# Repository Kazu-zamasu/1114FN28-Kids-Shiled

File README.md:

1114FN28-Kids-Shiled
==================================
超簡単な概要
#趣旨
mbedなりArduinoなりでArduino Pin Cnvertible の場合に高級なシールドだけじゃなく子供でも遊べる簡単なシールドを作る。  
Lチカでもモーターでも遊べるように。また、コードから制御するのではなく、視覚的、感覚的に分かりやすいVolや照度や温度などで遊べる基本的な制御を学べるボードにする。  
できれば、販売価格は小学校高学年とかその年齢層でもお年玉とか、日頃のプレゼントで買って貰えそうな値段に抑えたい。  
尚、本プロジェクトは完全ボランティアなので必要な経費をそのまま売価にします。よって、設計費用等の人件費はいっさい含みません。実際にお金を支払うもの以外は完全手弁当プロジェクトです。（とりあえず）

//ピン仕様:Arduinoピン配列に準拠  
ピン仕様はスイッチサイエンス　mbed 1114FN28  
mbed LPC1114FN28  に対応としました。
http://www.switch-science.com/catalog/1714/  

##最終仕様：Rev0
mbed 1114FN28 に対応するのでプロジェクト名自体を変更
###ハード仕様
１）ボリュームによるアナログ入力  
２）LED２個（5v抵抗あり）緑・赤  
３）最大９A　MOS-FET(モータドライバ兼用） 
４）フォトICによる照度のアナログ入力  
５）サーミスタによる温度のアナログ入力  
６）タクトスイッチ２個によるデジタル入力  
７）トグルスイッチによるデジタル入力  

##改訂前  
####ハード仕様（must)  
1)可変抵抗２つ（ノブ付）  
2)フォトトランジスタ１つ  
3)LED4つ  赤・青・緑・黄
4)最大3V、2Aのモータドライバ出力2つ（FA130、3VStall電流値より）  
5)サーミスター２つ  
6)単３電池ボックス  
7)3Pスイッチ1つ、2Pスイッチ1つ  

####ハード仕様(Addtional)  
1)電圧入力を入れる場合は逆接保護回路  
2)全てリード部品にて接続。なるべく表面実装を避ける  
3)可能なら7セグ  
4)
な感じ。適時アプデします。 
上記のAuduinoシールドはこれをクローズしたら考えます。

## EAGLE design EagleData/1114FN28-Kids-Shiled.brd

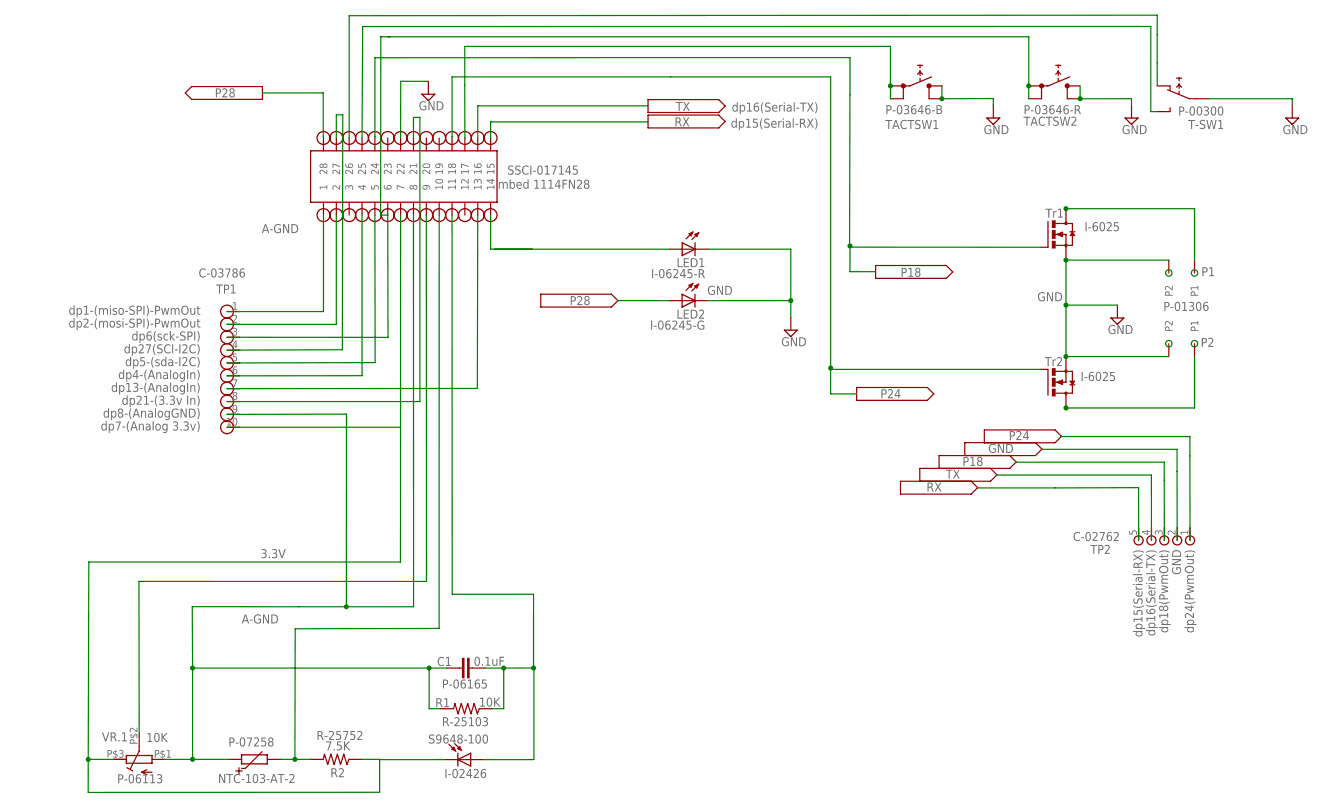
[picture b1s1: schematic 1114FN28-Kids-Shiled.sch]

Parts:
0-50C: NTC-103-AT-2; NTC
C1: 0.1uF; C
LED1: I-06245-R; LED5MM
LED2: I-06245-G; LED5MM
R1: 10K; R12MM
R2: 7.5K; R12MM
T-SW1: P-00300; TOGLE-SW
TACTSW1: P-03646-B; TACT-SW
TACTSW2: P-03646-R; TACT-SW
TB1, TB2: P-01306; TB
U$1: FH-1X14; DIP28-SOCKET
U$2: S9648-100; PHOTO-IC
U$3: SIPS-5
U$4, U$5: I-6025; TO251AA
U$8: SIPS-10
VR.1: 10K; VOL-TRIM

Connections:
3.3V: R2.1, U$1.P$7 (7), U$2.P$2 (C), U$8.10, VR.1.P$3 (E)
A-GND: 0-50C.1, C1.1, R1.2, U$1.P$8 (8), U$8.9, VR.1.P$1 (A)
GND: LED1.K (C), LED2.K (C), T-SW1.P$2 (2COM), TACTSW1.1 (4), TACTSW1.2, TACTSW2.1 (4), TACTSW2.2, TB1.P$2 (P2), TB2.P$2 (P2), U$1.P$22 (22), U$3.2, U$4.3 (S), U$5.3 (S)
unnamed: C1.2, R1.1, U$1.P$11 (11), U$2.P$1 (A)
unnamed: U$1.P$9 (9), VR.1.P$2 (S)
unnamed: TACTSW1.3, TACTSW1.4 (1), U$1.P$17 (17)
unnamed: U$1.P$1 (1), U$8.1
unnamed: U$1.P$5 (5), U$8.5
unnamed: U$1.P$27 (27), U$8.4
unnamed: T-SW1.P$3 (3), U$1.P$25 (25)
unnamed: U$1.P$2 (2), U$8.2
unnamed: TACTSW2.3, TACTSW2.4 (1), U$1.P$6 (6), U$8.3
unnamed: U$1.P$4 (4), U$8.6
unnamed: T-SW1.P$1 (1), U$1.P$26 (26)
unnamed: TB2.P$1 (P1), U$5.2 (D), U$5.4 (D)
unnamed: TB1.P$1 (P1), U$4.2 (D), U$4.4 (D)
unnamed: U$1.P$13 (13), U$8.7
unnamed: 0-50C.2, R2.2, U$1.P$10 (10)
unnamed: U$1.P$21 (21), U$8.8
P14: LED1.A, U$1.P$14 (14)
P18: U$1.P$18 (18), U$3.3, U$4.1 (G)
P24: U$1.P$24 (24), U$3.1, U$5.1 (G)
P28: LED2.A, U$1.P$28 (28)
RX: U$1.P$15 (15), U$3.5
TX: U$1.P$16 (16), U$3.4

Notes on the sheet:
dp13-(AnalogIn)
dp1-(miso-SPI)-PwmOut
dp2-(mosi-SPI)-PwmOut
dp6(sck-SPI)
dp27(SCl-I2C)
dp5-(sda-I2C)
dp4-(AnalogIn)
dp15(Serial-RX)
dp16(Serial-TX)
dp8-(AnalogGND)
TP1
Tr1
Tr2
mbed 1114FN28
P-01306
P-07258
P-06113
R-25103
P-06165
R-25752
I-02426
C-03786
SSCI-017145
dp21-(3.3v In)
TP2
C-02762
dp7-(Analog 3.3v)
dp24(PwmOut)
GND
dp18(PwmOut)

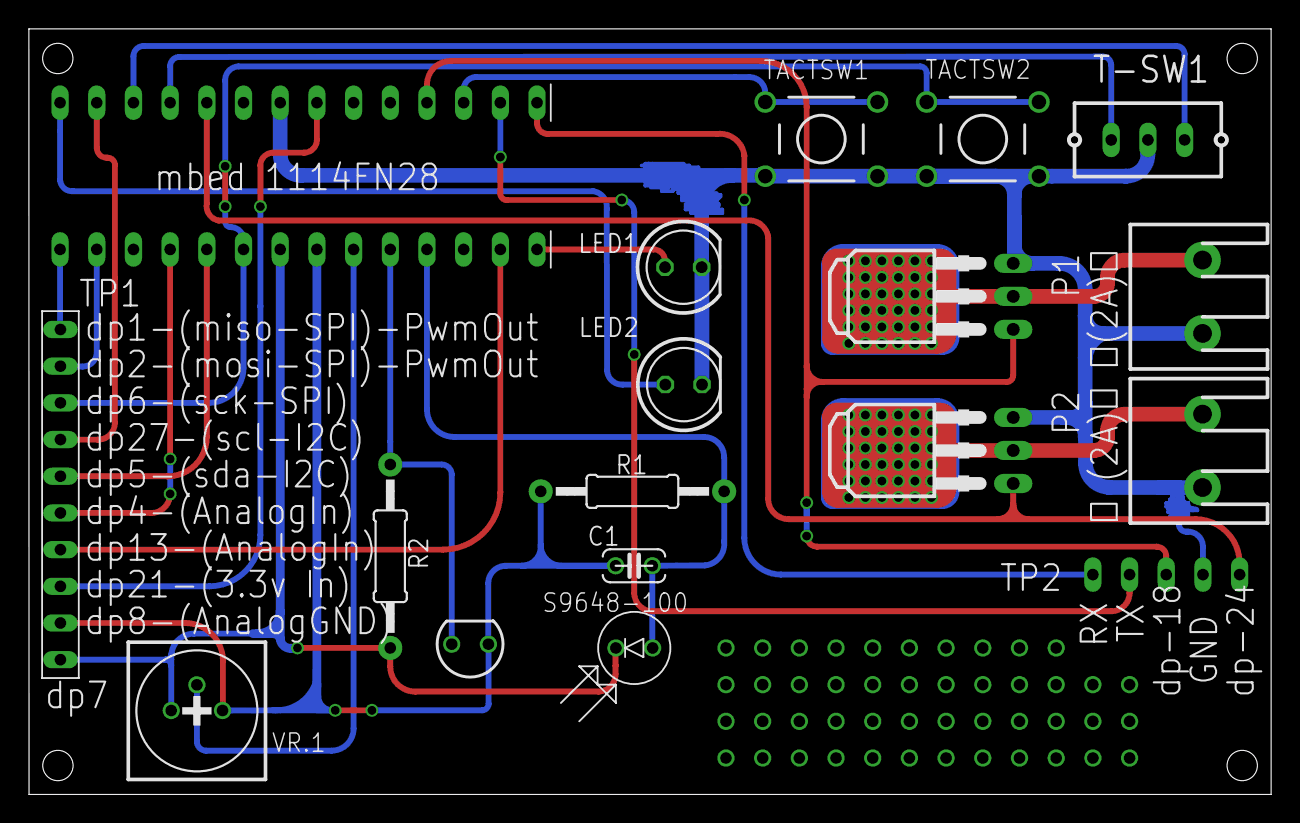
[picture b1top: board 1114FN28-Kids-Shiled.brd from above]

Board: 2 copper layers, 86.0 x 53.0 mm, 19 parts (1 on the bottom side), 25 nets.

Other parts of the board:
U$7: A4L-LOC

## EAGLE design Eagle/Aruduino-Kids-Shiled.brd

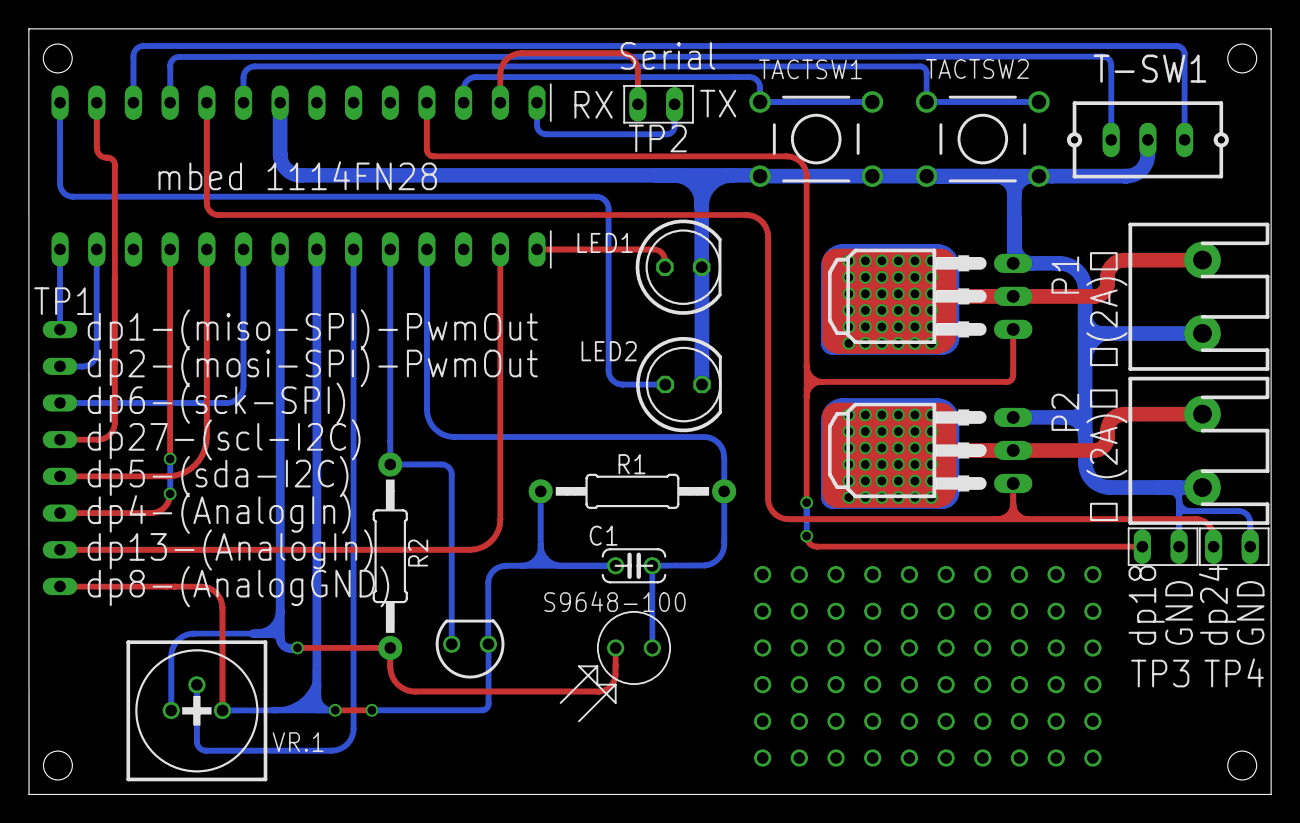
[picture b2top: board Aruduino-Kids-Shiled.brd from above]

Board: 2 copper layers, 86.0 x 53.0 mm, 21 parts (0 on the bottom side), 25 nets.

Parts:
0-50C: NTC-103-AT-2; NTC
C1: 0.1uF; C
LED1: I-06245-R; LED5MM
LED2: I-06245-G; LED5MM
R1: 10K; R12MM
R2: 7.5K; R12MM
T-SW1: P-00300; TOGLE-SW
TACTSW1: P-03646-B; TACT-SW
TACTSW2: P-03646-R; TACT-SW
TB1, TB2: P-01306; TB
U$1: FH-1X14; DIP28-SOCKET
U$2: S9648-100; PHOTO-IC
U$3: SIPS-7; SIPC-7
U$4: IR-6050; TO251AA
U$5: IR6050; TO251AA
U$6, U$9, U$10: SIPS-2; SIPC-2
U$7: A4L-LOC
VR.1: 10K; VOL-TRIM

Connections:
3.3V: R2.1, U$1.P$7, U$2.P$2, VR.1.P$3
A-GND: 0-50C.1, C1.1, R1.2, U$1.P$8, U$3.P$8, VR.1.P$1
GND: LED1.K, LED2.K, T-SW1.P$2, TACTSW1.1, TACTSW1.2, TACTSW2.1, TACTSW2.2, TB1.P$2, TB2.P$2, U$1.P$22, U$4.3, U$5.3, U$9.P$2, U$10.P$2
unnamed: C1.2, R1.1, U$1.P$11, U$2.P$1
unnamed: U$1.P$9, VR.1.P$2
unnamed: TACTSW1.3, TACTSW1.4, U$1.P$17
unnamed: U$1.P$1, U$3.P$1
unnamed: TACTSW2.3, TACTSW2.4, U$1.P$23
unnamed: U$1.P$27, U$3.P$4
unnamed: T-SW1.P$3, U$1.P$25
unnamed: U$1.P$2, U$3.P$2
unnamed: U$1.P$6, U$3.P$3
unnamed: U$1.P$5, U$3.P$5
unnamed: U$1.P$4, U$3.P$6
unnamed: T-SW1.P$1, U$1.P$26
unnamed: TB2.P$1, U$5.2, U$5.4
unnamed: TB1.P$1, U$4.2, U$4.4
unnamed: U$1.P$13, U$3.P$7
unnamed: U$1.P$16, U$6.P$1
unnamed: U$1.P$15, U$6.P$2
unnamed: 0-50C.2, R2.2, U$1.P$10
P14: LED1.A, U$1.P$14
P18: U$1.P$18, U$4.1, U$10.P$1
P24: U$1.P$24, U$5.1, U$9.P$1
P28: LED2.A, U$1.P$28

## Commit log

2014-05-20 Create BOM
2014-05-20 Update BOM
2014-05-20 Rename BOM to BOM.md
2014-07-04 Eagle-data
    First-commit
2014-07-04 Second
    few changes
2014-07-05 Semi_Final
2014-07-05 SemiFinal2
2014-07-06 Practice-Final
    Test-Build
2014-07-06 NEWBACK
2014-07-07 Final-P-ban
    1st time
2014-07-07 Test-Sample-Build
    Jet-PCB
2014-07-09 Add dimensions
2014-07-09 ProductRev0
2014-07-10 Change to Dril hole size
    2.00 to 2.1
2014-07-11 Sch layout change
2014-07-12 Chnge TP
2014-07-14 Change Sch
2014-07-14 Create main.cpp
    ボード用サンプルプログラム 機能確認用
2014-07-14 First CAM
2014-07-14 first
2014-07-14 Bord update
2015-01-15 Change to FET part number.
    I-6050 to I-6025 AKIZUKI part number.
    IRLU3410PBF
2015-01-15 Change to FET
    I-6050 to I-6025 AKIZUKI part number.
    IRLU3410PBF
2015-06-10 Rev5
    Rev5 update
2017-05-29 Added Untitled Diagram.xml
